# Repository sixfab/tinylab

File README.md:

# tinylab
[tinylab](https://sixfab.com/product/tinylab-exclusive-kit/) : prototype easier than ever

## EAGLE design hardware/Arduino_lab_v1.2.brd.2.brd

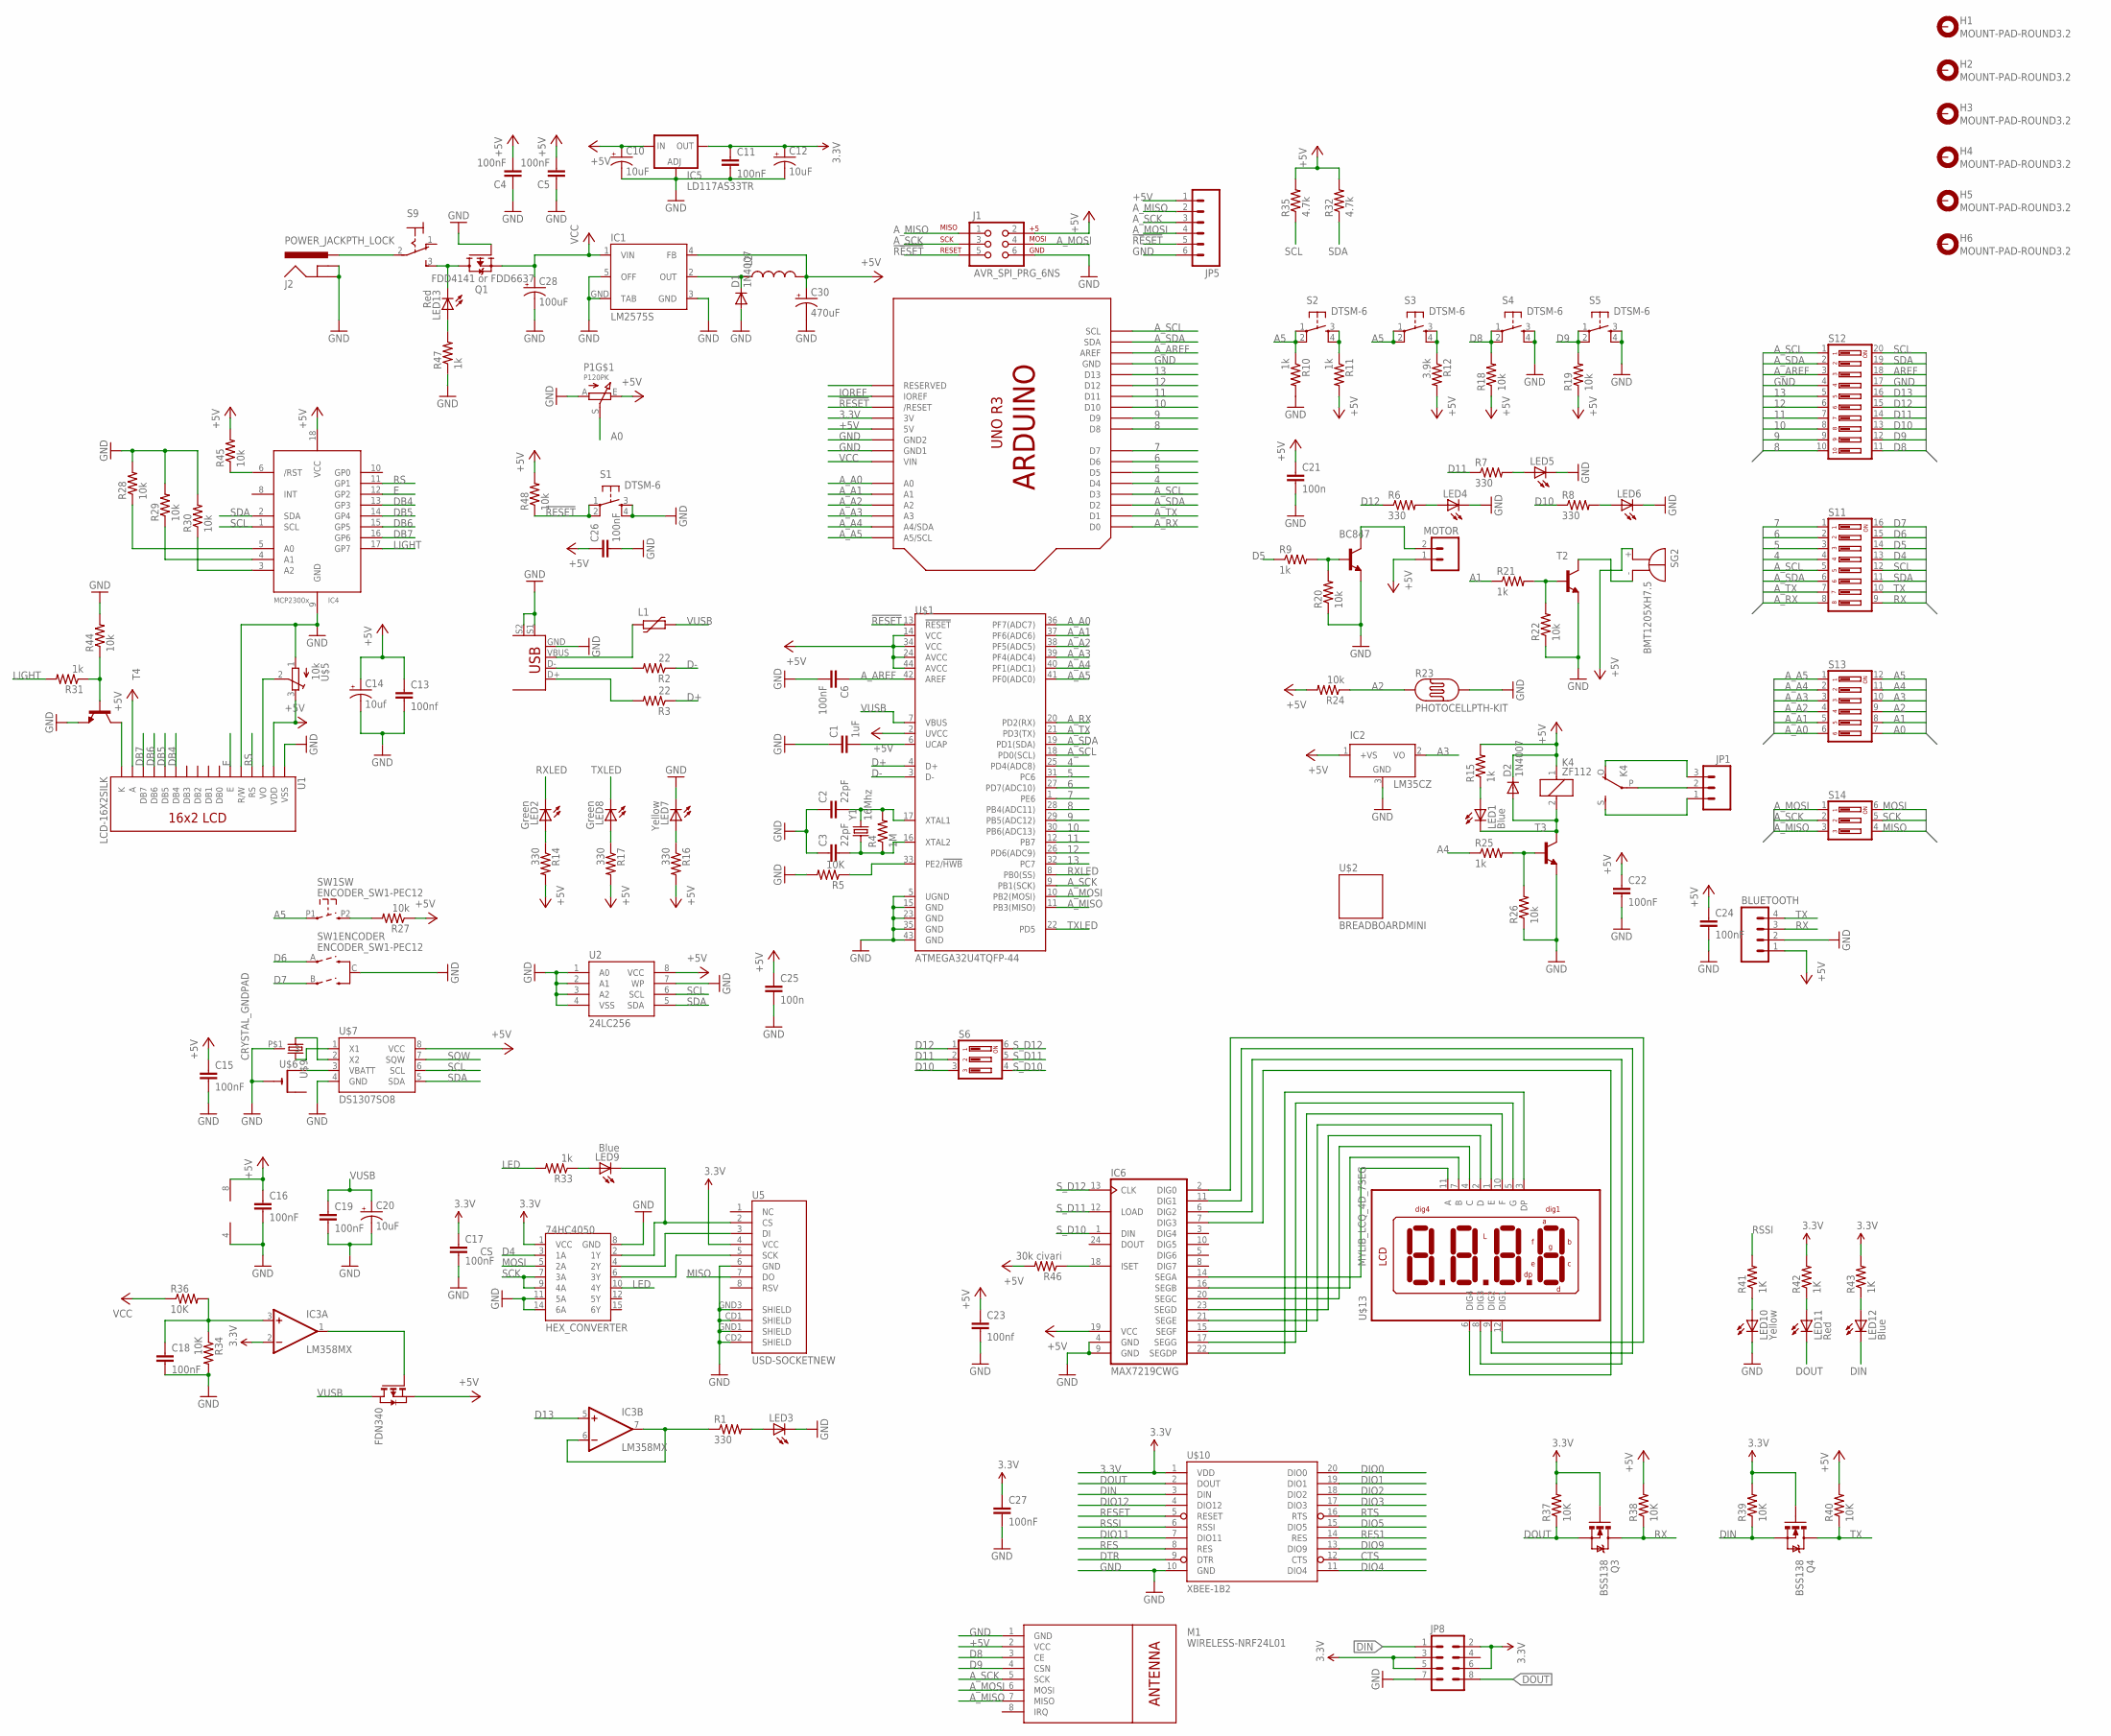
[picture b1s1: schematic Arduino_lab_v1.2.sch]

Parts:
74HC4050: HEX_CONVERTER; SO016
BC847: MMBT2222ALT1-NPN-SOT23-BEC; SOT23-BEC
BLUETOOTH: M04PTH; 1X04
C1: 1uF; 1206
C2, C3: 22pF; 0805
C4, C5, C6, C11, C15, C16, C17, C18, C19, C22, C24, C26, C27: 100nF; 0805
C10, C12, C20: 10uF; EIA3216
C13, C23: 100nf; 0805
C14: 10uf; EIA3216
C21, C25: 100n; 0805
C28: 100uF; NIPPON_F80
C30: 470uF; PANASONIC_G
D1, D2: 1N4007; SMA-DIODE_ALT
FDN340: PMOSSOT23; SOT-23
H1, H2, H3, H4, H5, H6: MOUNT-PAD-ROUND3.2; 3,2-PAD
IC1: LM2575S; TO263-5
IC2: LM35CZ; TO92
IC3: LM358MX; SO08
IC4: MCP2300X/SO; SO18W
IC5: LD117AS33TR; SOT223
IC6: MAX7219CWG; SO24W
J1: AVR_SPI_PRG_6NS; 2X3-NS
J2: POWER_JACKPTH_LOCK; POWER_JACK_PTH_LOCK
JP1: M03-SCREW-5MM; SCREWTERMINAL-5MM-3
JP5: M06SIP; 1X06
JP8: M04X2; 2X4
K4: ZF112
L1: FUSE_PTC-0805; PTC0805
L2: INDUCTORPWR; CDRH125
LED1, LED9, LED12: Blue; CHIPLED_0805
LED2, LED8: Green; CHIPLED_0805
LED3, LED4, LED5, LED6: LED5MM
LED7, LED10: Yellow; CHIPLED_0805
LED11, LED13: Red; CHIPLED_0805
M1: WIRELESS-NRF24L01
MOTOR: M023.5MM; SCREWTERMINAL-3.5MM-2
P1: P120PK
Q1: FDD4141 or FDD6637; TO252
Q3, Q4: BSS138; SOT23-3
R1, R6, R7, R8, R14, R16, R17: 330; 0805
R2, R3: 22; 0805
R4: 1M; 0805
R5, R34, R36, R37, R38, R39, R40: 10K; 0805
R9, R10, R11, R15, R21, R25, R31, R33, R47: 1k; 0805
R12: 3.9k; 0805
R18, R19, R20, R22, R24, R26, R27, R28, R29, R30, R44, R45, R48: 10k; 0805
R23: PHOTOCELLPTH-KIT; PHOTOCELL-KIT
R32, R35: 4.7k; 0805
R41, R42, R43: 1K; 0805
R46: 30k civari; 0805
S1, S2, S3, S4, S5: DTSM-6
S6, S14: DIP03YL
S9: M9040P
S11: DIP08YL
S12: DIP10YL
S13: DIP06YL
SG2: BMT1205XH7.5
SW1: ENCODER_SW1-PEC12; PEC12_INCREMENTAL_ENCODER
T2, T3, T4: MMBT2222ALT1-NPN-SOT23-BEC; SOT23-BEC
U1: LCD-16X2SILK; LCD-16X2
U2: 24LC256; SO08
U5: USD-SOCKETNEW; MICRO-SD-SOCKET-PP
U$1: ATMEGA32U4TQFP-44; TQFP44
U$2: BREADBOARDMINI; BREADBOARD-MINI
U$3: USB+SHIELD; USB-B-PTH
U$4: UNO_R3
U$5: 10k; TC33X
U$6: CR1220SMT; CR1220-SMD
U$7: DS1307SO8; SO08
U$9: CRYSTAL_GNDPAD; TC38H_GNDPAD
U$10: XBEE-1B2; XBEE-SILK
U$13: MYLIB_LCQ_4D_7SEG; MYLIB_LDQ_4D_7SEG
Y1: 16Mhz; CRYSTAL-SMD-5X3

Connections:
3.3V: 74HC4050.1 (VCC), C11.1, C12.A (+), C17.1, C27.1, IC3.2 (-IN), IC5.4 (OUT), JP8.2, JP8.3, JP8.5, JP8.6, Q3.1 (G), Q4.1 (G), R37.2, R39.2, R42.2, R43.2, U5.4 (VCC), U$4.3V, U$10.1 (VDD)
4: S11.4, U$1.25 (PD4(ADC8)), U$4.D4
5: S11.3, U$1.31 (PC6), U$4.D5
6: S11.2, U$1.27 (PD7(ADC10)), U$4.D6
7: S11.1, U$1.1 (PE6), U$4.D7
8: S12.10, U$1.28 (PB4(ADC11)), U$4.D8
9: S12.9, U$1.29 (PB5(ADC12)), U$4.D9
10: S12.8, U$1.30 (PB6(ADC13)), U$4.D10
11: S12.7, U$1.12 (PB7), U$4.D11
12: S12.6, U$1.26 (PD6(ADC9)), U$4.D12
13: S12.5, U$1.32 (PC7), U$4.D13
!RESET: J1.5, JP5.5, R48.1, S1.1, S1.2, U$1.13 (!RESET), U$4.RESET (/RESET)
+5V: BLUETOOTH.1, C4.2, C5.2, C10.A (+), C13.1, C14.A (+), C15.1, C16.1, C21.1, C22.1, C23.1, C24.1, C25.1, C26.1, C30.+, D2.C, FDN340.2 (S), IC1.4 (FB), IC2.1 (+VS), IC3.8 (V+), IC4.18 (VCC), IC5.3 (IN), IC6.19 (VCC), J1.2, JP5.1, K4.1, L2.2, M1.2 (VCC), MOTOR.1, P1.E, R11.2, R12.2, R14.2, R15.2, R16.2, R17.2, R18.1, R19.1, R24.2, R27.1, R32.2, R35.2, R38.2, R40.2, R45.2, R46.2, R48.2, SG2.+, U1.2 (VDD), U1.15 (A), U2.8 (VCC), U$1.2 (UVCC), U$1.14 (VCC), U$1.24 (AVCC), U$1.34 (VCC), U$1.44 (AVCC), U$4.5V, U$5.3 (E), U$7.8 (VCC)
A0: P1.S, S13.7
A1: R21.1, S13.8
A2: R23.1, R24.1, S13.9
A3: IC2.2 (VO), S13.10
A4: R25.1, S13.11
A5: R10.1, S2.1, S2.2, S3.1, S3.2, S13.12, SW1.P1 (1)
AREF: S12.18
A_A0: S13.6, U$1.36 (PF7(ADC7)), U$4.A0
A_A1: S13.5, U$1.37 (PF6(ADC6)), U$4.A1
A_A2: S13.4, U$1.38 (PF5(ADC5)), U$4.A2
A_A3: S13.3, U$1.39 (PF4(ADC4)), U$4.A3
A_A4: S13.2, U$1.40 (PF1(ADC1)), U$4.A4 (A4/SDA)
A_A5: S13.1, U$1.41 (PF0(ADC0)), U$4.A5 (A5/SCL)
A_AREF: C6.1, S12.3, U$1.42 (AREF), U$4.AREF
A_MISO: J1.1, JP5.2, M1.7 (MISO), S14.3, U$1.11 (PB3(MISO))
A_MOSI: J1.4, JP5.4, M1.6 (MOSI), S14.1, U$1.10 (PB2(MOSI))
A_RX: S11.8, U$1.20 (PD2(RX)), U$4.D0
A_SCK: J1.3, JP5.3, M1.5 (SCK), S14.2, U$1.9 (PB1(SCK))
A_SCL: S11.5, S12.1, U$1.18 (PD0(SCL)), U$4.D3, U$4.SCL
A_SDA: S11.6, S12.2, U$1.19 (PD1(SDA)), U$4.D2, U$4.SDA
A_TX: S11.7, U$1.21 (PD3(TX)), U$4.D1
CTS: U$10.12 (CTS)
D4: 74HC4050.3 (1A), S11.13
D5: R9.1, S11.14
D6: S11.15, SW1.A
D7: S11.16, SW1.B
D8: M1.3 (CE), R18.2, S4.1, S4.2, S12.11
D9: M1.4 (CSN), R19.2, S5.1, S5.2, S12.12
D10: R8.1, S6.3, S12.13
D11: R7.1, S6.2, S12.14
D12: R6.1, S6.1, S12.15
D13: IC3.5 (+IN), S12.16
D+: R3.1, U$1.4 (D+)
D-: R2.1, U$1.3 (D-)
DB4: IC4.13 (GP3), U1.11 (DB4)
DB5: IC4.14 (GP4), U1.12 (DB5)
DB6: IC4.15 (GP5), U1.13 (DB6)
DB7: IC4.16 (GP6), U1.14 (DB7)
DIN: JP8.1, LED12.C, Q4.2 (S), R39.1, U$10.3 (DIN)
DIO0: U$10.20 (DIO0)
DIO1: U$10.19 (DIO1)
DIO2: U$10.18 (DIO2)
DIO3: U$10.17 (DIO3)
DIO4: U$10.11 (DIO4)
DIO5: U$10.15 (DIO5)
DIO9: U$10.13 (DIO9)
DIO11: U$10.7 (DIO11)
DIO12: U$10.4 (DIO12)
DOUT: JP8.8, LED11.C, Q3.2 (S), R37.1, U$10.2 (DOUT)
DTR: U$10.9 (DTR)
E: IC4.12 (GP2), U1.6 (E)
GND: 74HC4050.8 (GND), 74HC4050.11 (5A), 74HC4050.14 (6A), BC847.E, BLUETOOTH.2, C1.1, C2.1, C3.1, C4.1, C5.1, C6.2, C10.C (-), C11.2, C12.C (-), C13.2, C14.C (-), C15.2, C16.2, C17.2, C18.2, C19.2, C20.C (-), C21.2, C22.2, C23.2, C24.2, C25.2, C26.2, C27.2, C28.-, C30.-, D1.A, IC1.3 (GND), IC1.5 (OFF), IC1.GND (TAB), IC2.3 (GND), IC3.4 (V-), IC4.9 (GND), IC5.1 (ADJ), IC6.4 (GND), IC6.9 (GND), J1.6, J2.GND, J2.GNDBREAK, JP5.6, JP8.7, LED3.K (C), LED4.K (C), LED5.K (C), LED6.K (C), LED7.C, LED10.C, M1.1 (GND), P1.A, Q1.1 (G), R5.2, R10.2, R20.1, R22.1, R23.2, R26.1, R28.2, R29.2, R30.2, R34.2, R44.2, R47.1, S1.3, S1.4, S4.3, S4.4, S5.3, S5.4, S12.4, S12.17, SW1.C, T2.E, T3.E, T4.E, U1.1 (VSS), U1.5 (R/W), U2.1 (A0), U2.2 (A1), U2.3 (A2), U2.4 (VSS), U2.7 (WP), U5.6 (GND), U5.CD1 (SHIELD), U5.CD2 (SHIELD), U5.GND1 (SHIELD), U5.GND3 (SHIELD), U$1.5 (UGND), U$1.15 (GND), U$1.23 (GND), U$1.35 (GND), U$1.43 (GND), U$3.GND, U$3.S1, U$3.S2, U$4.GND, U$4.GND1, U$4.GND2, U$5.1 (A), U$6.-, U$7.4 (GND), U$9.P$1 (3), U$10.10 (GND)
IOREF: U$4.IOREF
LED: 74HC4050.10 (4Y), R33.2
LIGHT: IC4.17 (GP7), R31.2
MISO: S14.4, U5.7 (DO)
MOSI: 74HC4050.5 (2A), S14.6
unnamed: R2.2, U$3.D-
unnamed: R3.2, U$3.D+
unnamed: LED3.A, R1.2
unnamed: C1.2, U$1.6 (UCAP)
unnamed: R11.1, S2.3, S2.4
unnamed: C3.2, R4.1, U$1.16 (XTAL2), Y1.1
unnamed: C2.2, R4.2, U$1.17 (XTAL1), Y1.3 (2)
unnamed: R21.2, R22.2, T2.B
unnamed: R5.1, U$1.33 (PE2/!HWB)
unnamed: D1.C, IC1.2 (OUT), L2.1
unnamed: R12.1, S3.3, S3.4
unnamed: BC847.B, R9.2, R20.2
unnamed: LED4.A, R6.2
unnamed: JP1.3, K4.O
unnamed: LED5.A, R7.2
unnamed: BC847.C, MOTOR.2
unnamed: LED6.A, R8.2
unnamed: SG2.-, T2.C
unnamed: LED1.A, R15.1
unnamed: R25.2, R26.2, T3.B
unnamed: D2.A, K4.2, LED1.C, T3.C
unnamed: LED2.A, R14.1
unnamed: LED8.A, R17.1
unnamed: JP1.2, K4.P
unnamed: JP1.1, K4.S
unnamed: J2.PWR, S9.2
unnamed: LED13.C, Q1.3 (D), S9.3 (S)
unnamed: IC4.5 (A0), R28.1
unnamed: IC4.4 (A1), R29.1
unnamed: IC4.3 (A2), R30.1
unnamed: R27.2, SW1.P2 (2)
unnamed: R31.1, R44.1, T4.B
unnamed: U1.3 (VO), U$5.2 (S)
unnamed: T4.C, U1.16 (K)
unnamed: U$7.2 (X2), U$9.1
unnamed: U$6.+$1 (+), U$7.3 (VBATT)
unnamed: IC6.14 (SEGA), U$13.11 (A)
unnamed: 74HC4050.4 (2Y), U5.3 (DI)
unnamed: 74HC4050.6 (3Y), U5.5 (SCK)
unnamed: U$7.1 (X1), U$9.2
unnamed: LED9.A, R33.1
unnamed: 74HC4050.2 (1Y), LED9.C, U5.2 (CS)
unnamed: L1.1, U$3.VBUS
unnamed: C18.1, IC3.3 (+IN), R34.1, R36.2
unnamed: LED10.A, R41.1
unnamed: FDN340.3 (G), IC3.1 (OUT)
unnamed: IC3.6 (-IN), IC3.7 (OUT), R1.1
unnamed: LED11.A, R42.1
unnamed: LED12.A, R43.1
unnamed: LED13.A, R47.2
unnamed: IC4.6 (/RST), R45.1
unnamed: IC6.18 (ISET), R46.1
unnamed: IC6.16 (SEGB), U$13.7 (B)
unnamed: IC6.20 (SEGC), U$13.4 (C)
unnamed: IC6.23 (SEGD), U$13.2 (D)
unnamed: IC6.21 (SEGE), U$13.1 (E)
unnamed: IC6.15 (SEGF), U$13.10 (F)
unnamed: IC6.17 (SEGG), U$13.5 (G)
unnamed: IC6.22 (SEGDP), U$13.3 (DP)
unnamed: IC6.7 (DIG3), U$13.6 (DIG4)
unnamed: IC6.6 (DIG2), U$13.8 (DIG3)
unnamed: IC6.11 (DIG1), U$13.9 (DIG2)
unnamed: IC6.2 (DIG0), U$13.12 (DIG1)
unnamed: LED7.A, R16.1
RES: U$10.8 (RES)
RES1: U$10.14 (RES)
RESET: U$10.5 (RESET)
RS: IC4.11 (GP1), U1.4 (RS)
RSSI: R41.2, U$10.6 (RSSI)
RTS: U$10.16 (RTS)
RX: BLUETOOTH.3, Q3.3 (D), R38.1, S11.9
RXLED: LED2.C, U$1.8 (PB0(SS))
SCK: 74HC4050.7 (3A), 74HC4050.9 (4A), S14.5
SCL: IC4.1 (SCL), R35.1, S11.12, S12.20, U2.6 (SCL), U$7.6 (SCL)
SDA: IC4.2 (SDA), R32.1, S11.11, S12.19, U2.5 (SDA), U$7.5 (SDA)
SQW: U$7.7 (SQW)
S_D10: IC6.1 (DIN), S6.4
S_D11: IC6.12 (LOAD), S6.5
S_D12: IC6.13 (CLK), S6.6
TX: BLUETOOTH.4, Q4.3 (D), R40.1, S11.10
TXLED: LED8.C, U$1.22 (PD5)
VCC: C28.+, IC1.1 (VIN), Q1.2 (S), R36.1, U$4.VIN
VUSB: C19.1, C20.A (+), FDN340.1 (D), L1.2, U$1.7 (VBUS)

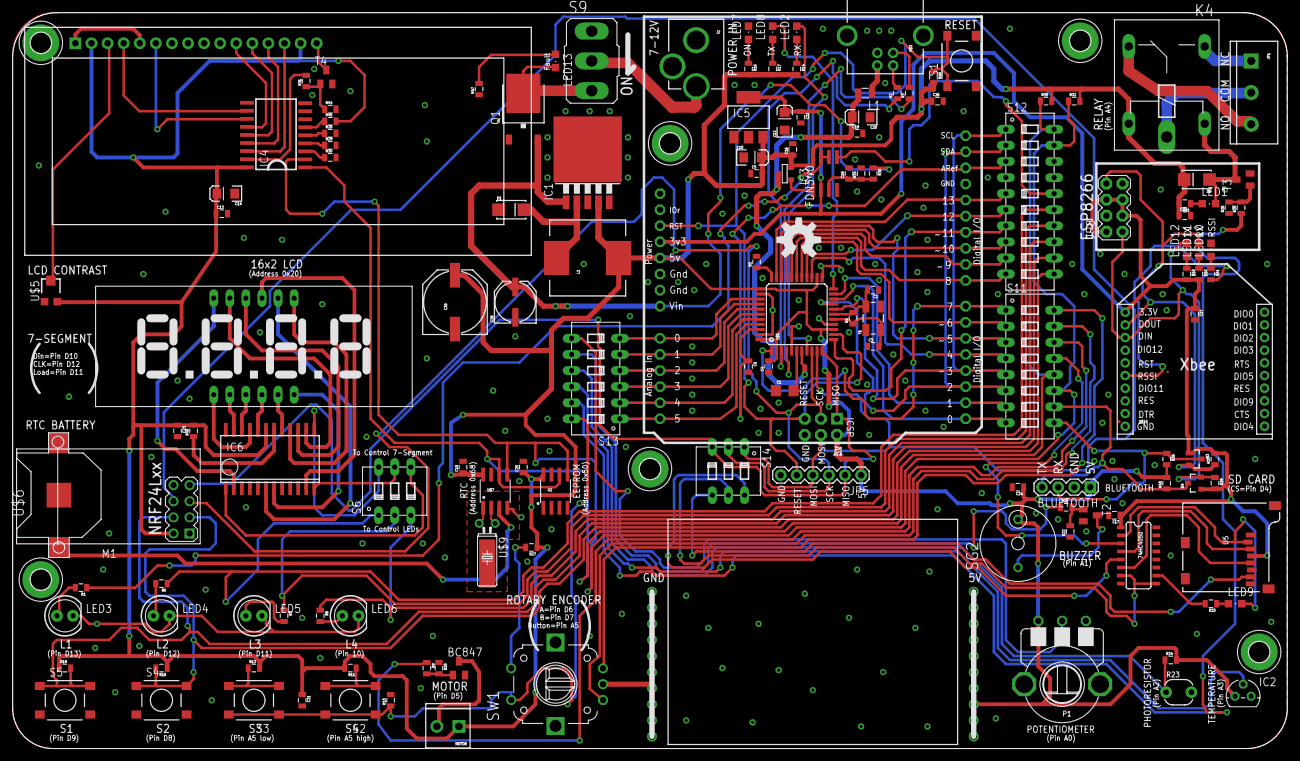
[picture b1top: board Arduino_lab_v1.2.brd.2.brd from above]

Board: 2 copper layers, 201.3 x 116.2 mm, 151 parts (0 on the bottom side), 135 nets.

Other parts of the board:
U$8: INDIEGOGO_FONT_LOGO
U$11: TINYLAB_LOGO_LARGE
U$14: OSHW-LOGO-L

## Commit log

2016-01-11 added hardware design files
2016-01-11 added mechanical parts of case
2016-01-11 added example codes of use cases
2016-01-11 Create LICENCE
2016-01-12 Update LICENCE
2016-01-19 added hardware schematic files on pdf format
2016-01-26 added and reorganized example codes of tinylab
2016-04-05 case is made suitable for molding.
2016-04-11 added stl files
2016-04-21 added extra magnet mounts and resized montage holes
2016-04-22 added resistor on lcd backlight led and done some little changes.
2016-06-17 Fixed Typo
2016-06-22 added tinylab test code
2016-08-02 fulfilled the display bug on rtc test
2016-08-11 fix typo
2016-08-16 Switch from SD library to SdFat library
    SD library is extremely large. SdFat library is much smaller and is fine for what this project does. Making this change lowers project size from 99% of maximum upload to 86% of maximum.
2016-08-17 rewrited SD codes as suitable for SdFat library
2016-08-17 added libraries that using at Tinylab test codes
2017-01-13 Company edit
2017-01-13 Remove
2017-01-19 LCD 7 segments example
2017-03-16 Update basic_digital_watch.ino
    Fix "Add Header"
2017-08-11 tinylab_test_code: Fix for extEEPROM 3.3.5
    The extEEPROM library available in tinylab/library is an old version where the enum twiClockFreq_t was defined globally.
    More recent versions of the extEEPROM library have moved the definition of clock frequency enumeration inside the class definition.
    See https://github.com/PaoloP74/extEEPROM/commit/1944b15231a1f71187e1cd163595b2b80981ab4c
    Prepend class namespace to fix the compilation issue.
    Tested with extEEPROM Library Version 3.3.5 (loaded by the Arduino Library Manager)
    Fix https://github.com/sixfab/tinylab/issues/6
2017-08-11 tinylab_test_code: Include TimeLib.h
    Fix compilation error
    In file included from ...\tinylab_test_code\tinylab_test_code.ino:30:0:
    ....\Arduino\libraries\DS1307RTC/DS1307RTC.h:19:22: errror: 'tmElements_t' has not been declared
    static bool read(tmElements_t &tm);
2017-11-08 removed old libraries and added new libraries for compatible with arduıino ide versiyon 1.8.5.
2017-11-08 updated tinylab test_code for suitable with new added libraries.
2017-11-08 updated DS130RTC library to version 1.4.0.
2017-11-08 updated extEEPROM library to version 3.3.5.
2017-11-08 updated ledControl library readme.md file
2017-11-08 updated RF24 library to version 1.3.0.
2017-11-08 updated SdFat library to version 1.0.3.
2017-11-08 update Time library to version 1.5.0.

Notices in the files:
parts and their libraries:
SparkFun-DigitalIC: Licensing: CC v3.0 Share-Alike You are welcome to use this library for commercial purposes.
SparkFun-Connectors: Licensing: Creative Commons ShareAlike 4.0 International - https://creativecommons.org/licenses/by-sa/4.0
